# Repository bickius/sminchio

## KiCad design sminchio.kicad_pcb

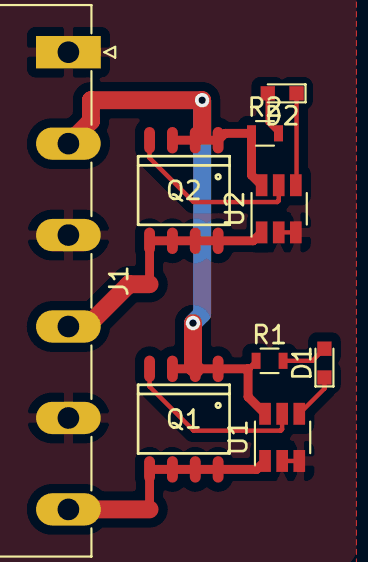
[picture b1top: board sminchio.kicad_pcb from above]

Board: 2 copper layers, 9 parts (0 on the bottom side), 10 nets.

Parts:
D1, D2: LED; LED_0603
J1: Screw_Terminal_01x06; PhoenixContact_MC-G_06x5.08mm_Angled
Q1, Q2: SQ4435EY; SO-8
R1, R2: 1.5 k; R_0603
U1, U2: LTC4412xS6; TSOT-23-6

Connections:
+12V: J1.2, Q1.1, Q1.2, Q1.3, Q2.1, Q2.2, Q2.3, R1.1, R2.1, U1.6, U2.6
GND: J1.1, J1.3, J1.5, U1.2, U1.3, U2.2, U2.3
unnamed: D1.1, U1.4
unnamed: D1.2, R1.2
unnamed: D2.1, U2.4
unnamed: D2.2, R2.2
unnamed: J1.4, Q2.5, Q2.6, Q2.7, Q2.8, U2.1
unnamed: J1.6, Q1.5, Q1.6, Q1.7, Q1.8, U1.1
unnamed: Q1.4, U1.5
unnamed: Q2.4, U2.5

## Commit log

2021-06-03 Update sminchio.kicad_pcb
    toccato il pcb
